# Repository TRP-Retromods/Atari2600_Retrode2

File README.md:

# Atari 2600 PLugin for Retrode 2
using SNES PCB style with a 3D printed part for fully support mechanical plug of the Atari 2600 games.

- Main PCB needs to be 1.2mm thick
- Patches for the socket needs to be 1.6mm with castellated vias

# Parts:
- 21x 100 ohms ressitor 0805
- 2x 10mm M2 screws
- 1x CONN CARDEDGE FEMALE 24POS 0.100 (https://www.digikey.ca/en/products/detail/te-connectivity-amp-connectors/5530843-1/2310824)

# Links:

https://hackaday.io/project/113217-atari2600-cartridge-reader

-- Retrode 2 website is down while I was publishing this --

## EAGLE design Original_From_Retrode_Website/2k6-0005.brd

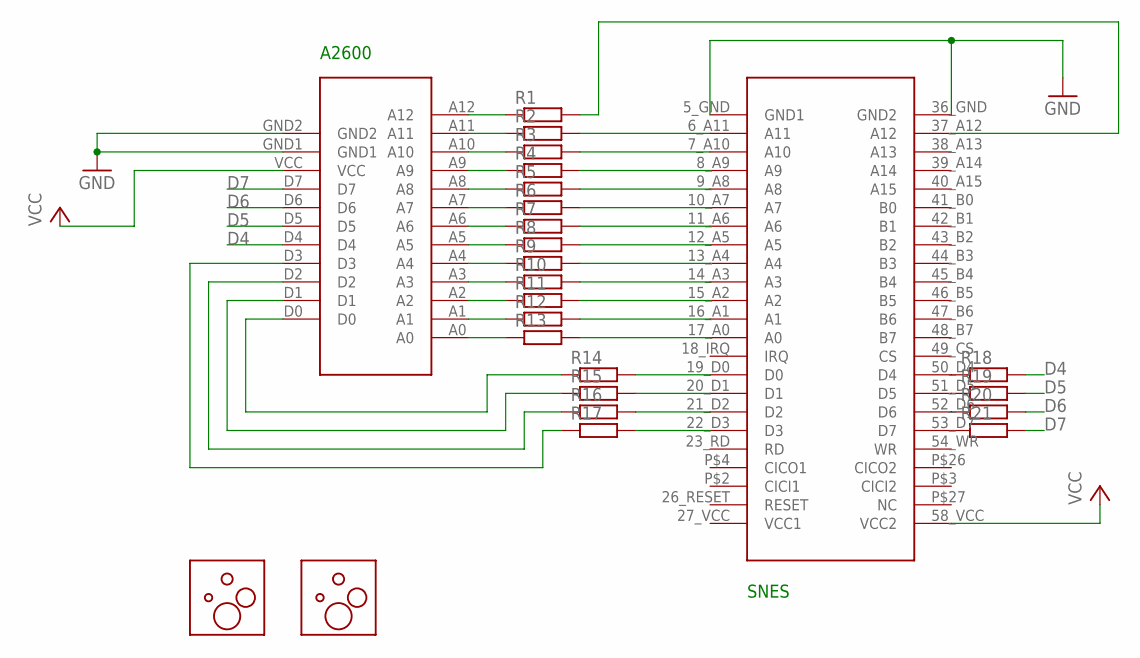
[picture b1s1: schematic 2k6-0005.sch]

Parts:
R1, R2, R3, R4, R5, R6, R7, R8, R9, R10, R11, R12, R13, R14, R15, R16, R17, R18, R19, R20, R21: R-EU_R0402; R0402
U$1: 2600CARTBIGGERPADS; 2600EDGE-BIGGER
U$2: SNESCART; SNESEDGE
U$3, U$4: STENCIL-ALIGN

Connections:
D4: R18.2, U$1.D4
D5: R19.2, U$1.D5
D6: R20.2, U$1.D6
D7: R21.2, U$1.D7
GND: U$1.GND1, U$1.GND2, U$2.5_GND (GND1), U$2.36_GND (GND2)
unnamed: R13.2, U$2.17_A0 (A0)
unnamed: R12.2, U$2.16_A1 (A1)
unnamed: R11.2, U$2.15_A2 (A2)
unnamed: R10.2, U$2.14_A3 (A3)
unnamed: R9.2, U$2.13_A4 (A4)
unnamed: R8.2, U$2.12_A5 (A5)
unnamed: R7.2, U$2.11_A6 (A6)
unnamed: R6.2, U$2.10_A7 (A7)
unnamed: R5.2, U$2.9_A8 (A8)
unnamed: R4.2, U$2.8_A9 (A9)
unnamed: R3.2, U$2.7_A10 (A10)
unnamed: R2.2, U$2.6_A11 (A11)
unnamed: R14.1, U$1.D0
unnamed: R15.1, U$1.D1
unnamed: R16.1, U$1.D2
unnamed: R17.1, U$1.D3
unnamed: R1.2, U$2.37_A12 (A12)
unnamed: R1.1, U$1.A12
unnamed: R2.1, U$1.A11
unnamed: R3.1, U$1.A10
unnamed: R4.1, U$1.A9
unnamed: R5.1, U$1.A8
unnamed: R6.1, U$1.A7
unnamed: R7.1, U$1.A6
unnamed: R8.1, U$1.A5
unnamed: R9.1, U$1.A4
unnamed: R10.1, U$1.A3
unnamed: R11.1, U$1.A2
unnamed: R12.1, U$1.A1
unnamed: R13.1, U$1.A0
unnamed: R14.2, U$2.19_D0 (D0)
unnamed: R16.2, U$2.21_D2 (D2)
unnamed: R15.2, U$2.20_D1 (D1)
unnamed: R17.2, U$2.22_D3 (D3)
unnamed: R18.1, U$2.50_D4 (D4)
unnamed: R19.1, U$2.51_D5 (D5)
unnamed: R20.1, U$2.52_D6 (D6)
unnamed: R21.1, U$2.53_D7 (D7)
VCC: U$1.VCC, U$2.58_VCC (VCC2)

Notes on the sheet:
A2600
SNES

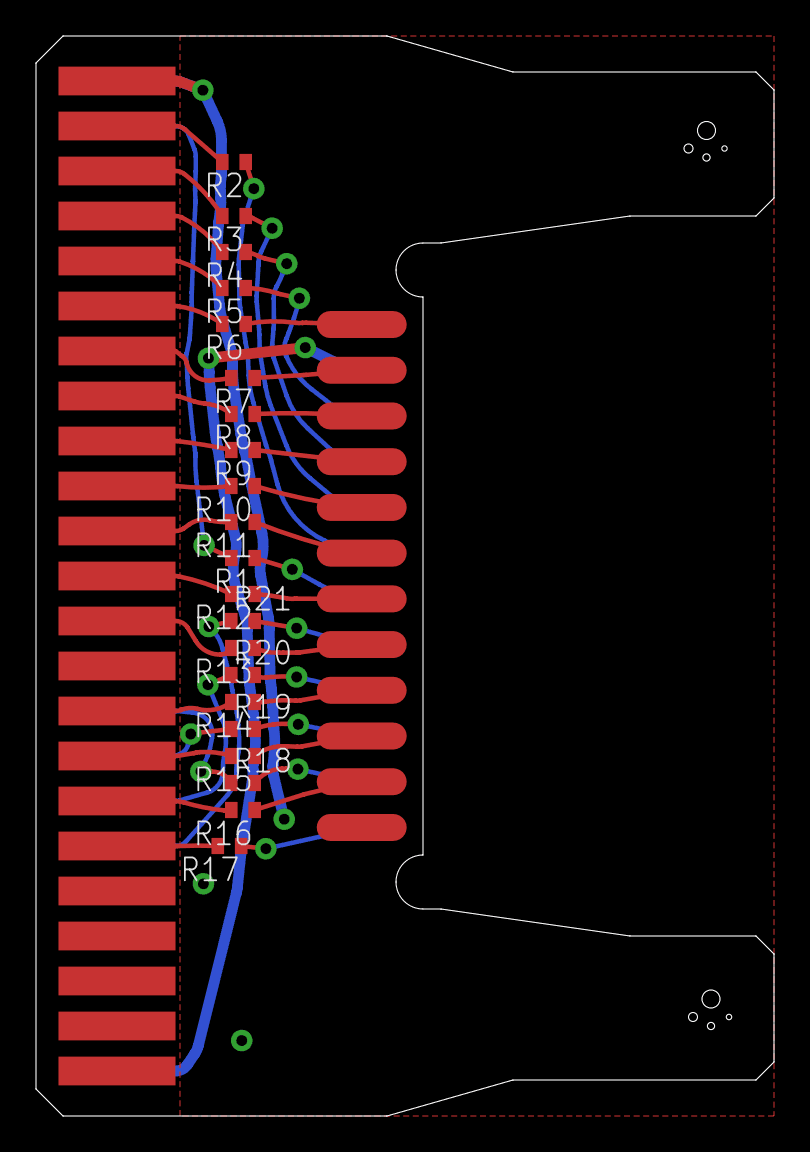
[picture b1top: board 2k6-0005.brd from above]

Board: 2 copper layers, 41.0 x 60.0 mm, 25 parts (1 on the bottom side), 44 nets.

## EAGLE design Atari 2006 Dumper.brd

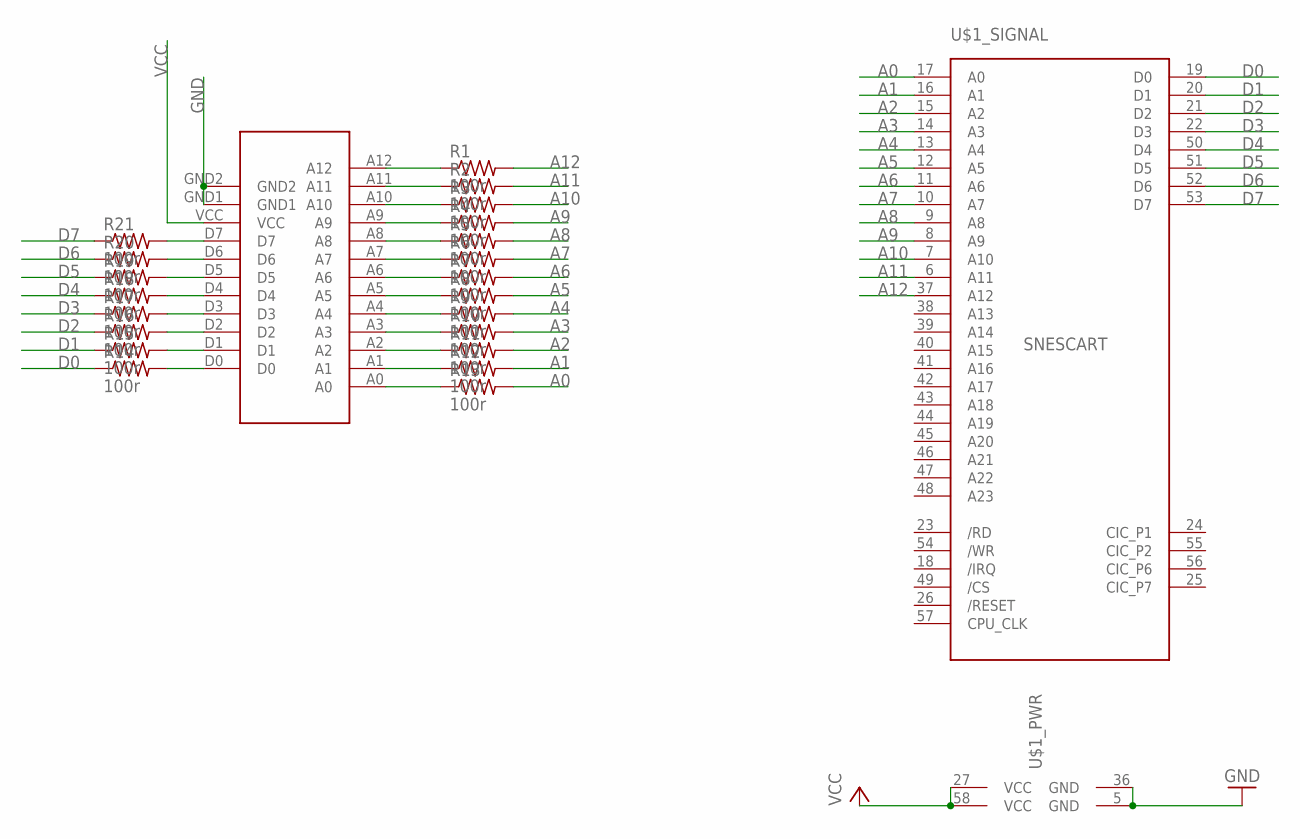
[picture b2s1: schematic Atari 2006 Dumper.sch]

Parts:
R1, R2, R3, R4, R5, R6, R7, R8, R9, R10, R11, R12, R13, R14, R15, R16, R17, R18, R19, R20, R21: 100r; R0603
U$1: SNESCART
U$2: 2600CARTBIGGERPADS; 2600EDGE-BIGGER

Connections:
A0: R13.2, U$1.17 (A0)
A1: R12.2, U$1.16 (A1)
A2: R11.2, U$1.15 (A2)
A3: R10.2, U$1.14 (A3)
A4: R9.2, U$1.13 (A4)
A5: R8.2, U$1.12 (A5)
A6: R7.2, U$1.11 (A6)
A7: R6.2, U$1.10 (A7)
A8: R5.2, U$1.9 (A8)
A9: R4.2, U$1.8 (A9)
A10: R3.2, U$1.7 (A10)
A11: R2.2, U$1.6 (A11)
A12: R1.2, U$1.37 (A12)
D0: R14.1, U$1.19 (D0)
D1: R15.1, U$1.20 (D1)
D2: R16.1, U$1.21 (D2)
D3: R17.1, U$1.22 (D3)
D4: R18.1, U$1.50 (D4)
D5: R19.1, U$1.51 (D5)
D6: R20.1, U$1.52 (D6)
D7: R21.1, U$1.53 (D7)
GND: U$1.5 (GND), U$1.36 (GND), U$2.GND1, U$2.GND2
unnamed: R1.1, U$2.A12
unnamed: R14.2, U$2.D0
unnamed: R13.1, U$2.A0
unnamed: R15.2, U$2.D1
unnamed: R16.2, U$2.D2
unnamed: R4.1, U$2.A9
unnamed: R3.1, U$2.A10
unnamed: R2.1, U$2.A11
unnamed: R5.1, U$2.A8
unnamed: R6.1, U$2.A7
unnamed: R7.1, U$2.A6
unnamed: R8.1, U$2.A5
unnamed: R9.1, U$2.A4
unnamed: R10.1, U$2.A3
unnamed: R11.1, U$2.A2
unnamed: R12.1, U$2.A1
unnamed: R17.2, U$2.D3
unnamed: R18.2, U$2.D4
unnamed: R19.2, U$2.D5
unnamed: R20.2, U$2.D6
unnamed: R21.2, U$2.D7
VCC: U$1.27 (VCC), U$1.58 (VCC), U$2.VCC

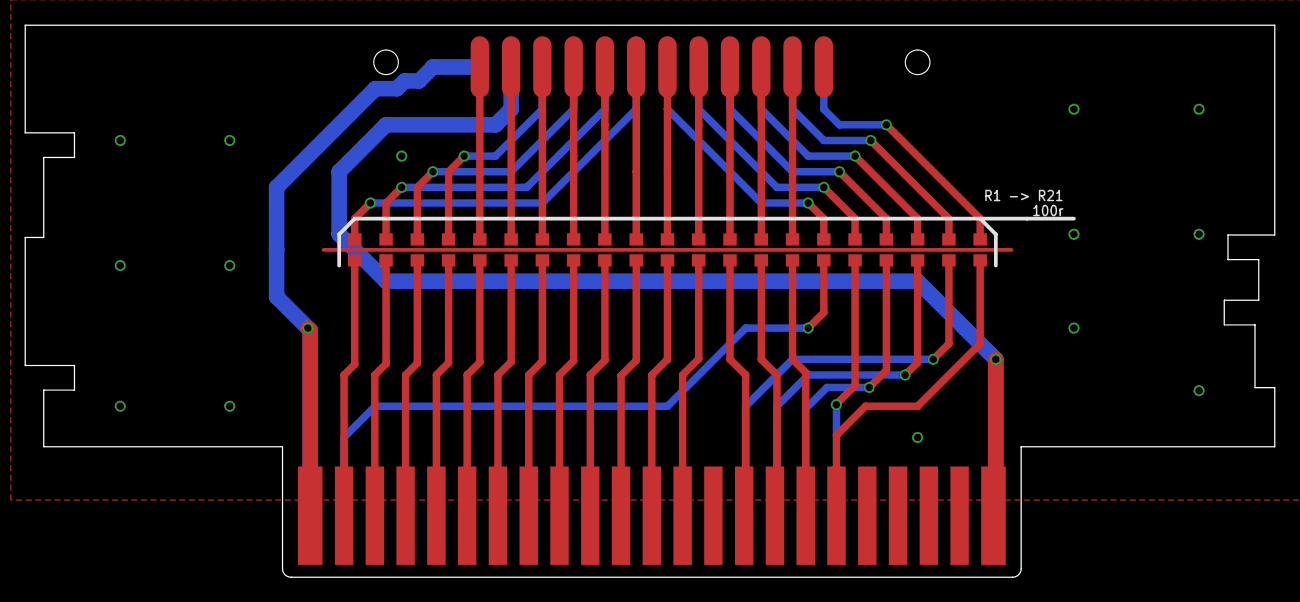
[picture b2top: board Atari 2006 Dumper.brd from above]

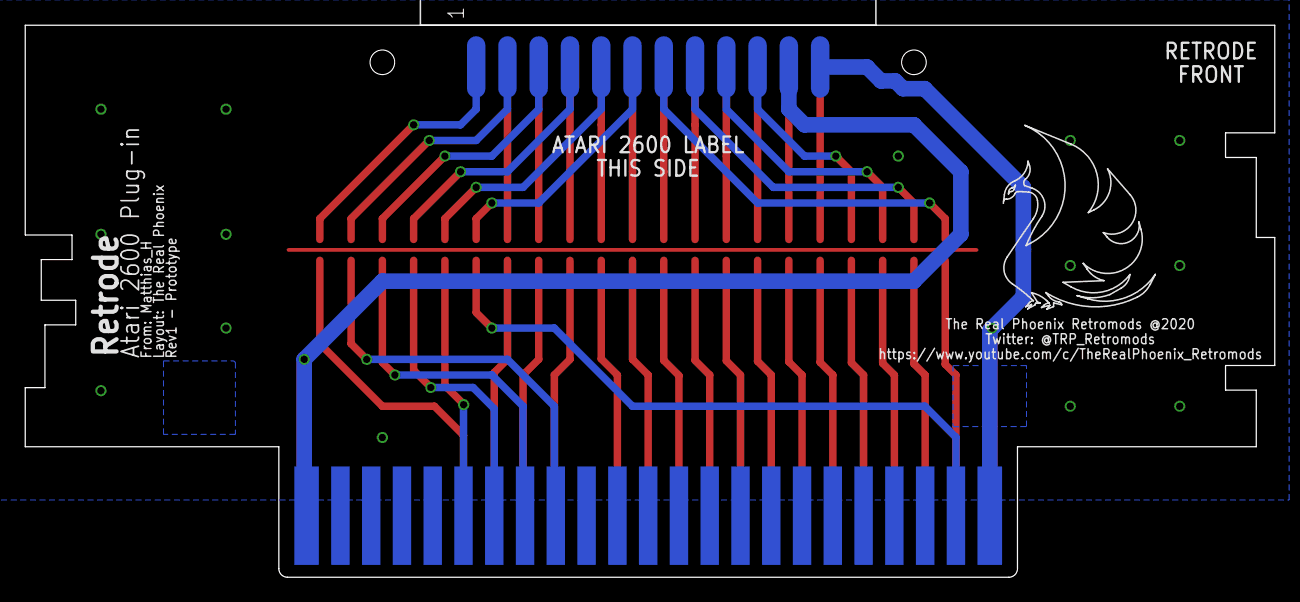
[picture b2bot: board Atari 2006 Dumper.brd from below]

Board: 2 copper layers, 101.5 x 44.8 mm, 24 parts (2 on the bottom side), 44 nets.

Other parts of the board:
U$3: LOGO

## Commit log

2021-04-12 Original Push
    First push with everything
2021-04-12 Update README.md
    Formating

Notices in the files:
Original_From_Retrode_Website/2k6-0005.brd:
(C) 2012
